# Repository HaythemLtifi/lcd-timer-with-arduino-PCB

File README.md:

# lcd-timer-with-arduino-PCB
Lcd timer with arduino that uses an encoder to set the time.
The code works but its limited , feel free to upgraded
Feel free to review the board.

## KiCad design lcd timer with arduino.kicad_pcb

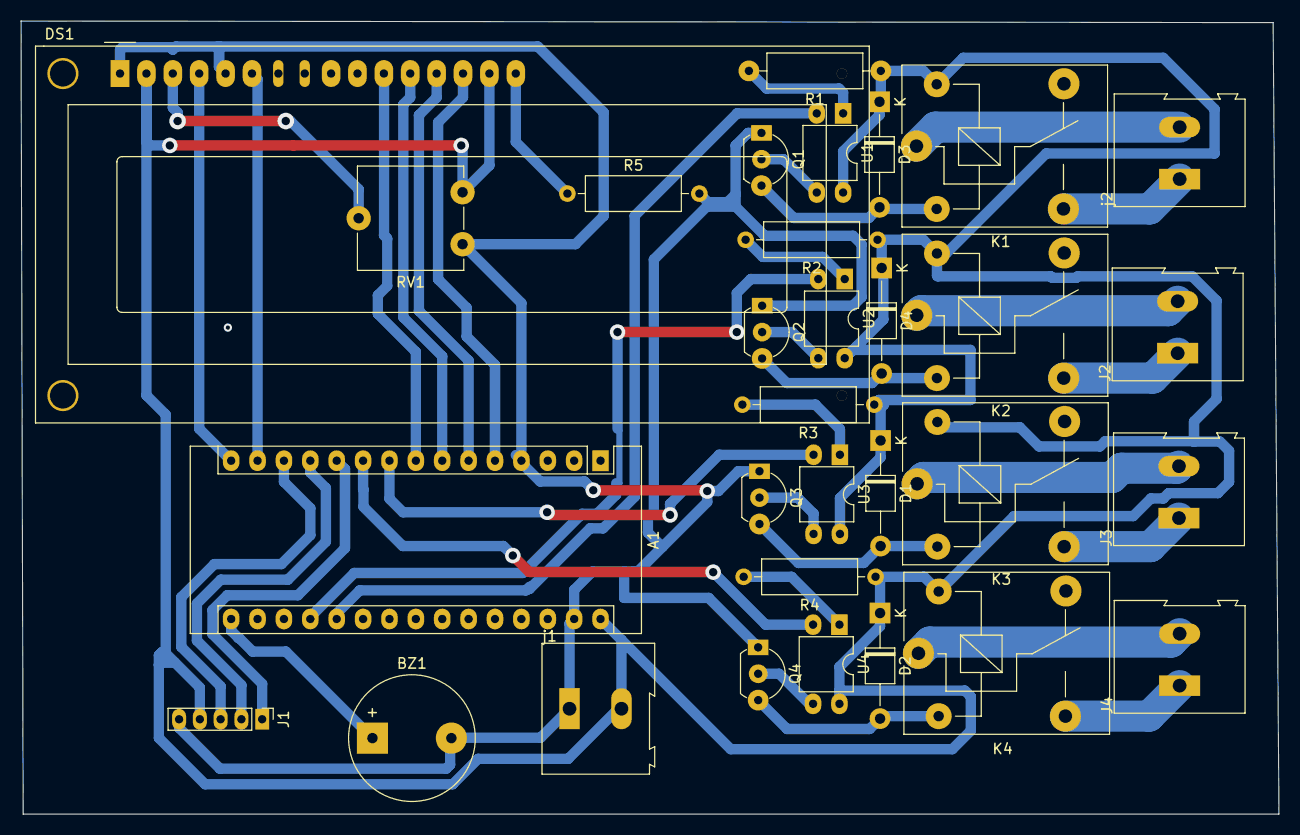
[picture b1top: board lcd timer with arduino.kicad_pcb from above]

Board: 2 copper layers, 121.1 x 76.4 mm, 31 parts (0 on the bottom side), 38 nets.

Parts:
A1: Arduino_Nano_v3.x; Arduino_Nano
BZ1: Buzzer; Buzzer_12x9.5RM7.6
D1, D2, D3, D4: D; D_T-1_P10.16mm_Horizontal
DS1: WC1602A
J1: Conn_01x05_Female; PinHeader_1x05_P2.00mm_Vertical
J2, J3, J4: Screw_Terminal_01x02; TerminalBlock_Altech_AK300-2_P5.00mm
K1, K2, K3, K4: SANYOU_SRD_Form_C; Relay_SPDT_SANYOU_SRD_Series_Form_C
Q1, Q2, Q3, Q4: 2N3904; TO-92L_Inline_Wide
R1, R2, R3, R4: 1k; R_Axial_DIN0309_L9.0mm_D3.2mm_P12.70mm_Horizontal
R5: 220; R_Axial_DIN0309_L9.0mm_D3.2mm_P12.70mm_Horizontal
RV1: R_POT; Potentiometer_ACP_CA9-V10_Vertical
U1, U2, U3, U4: PC817; DIP-4_W7.62mm
j1, j2: Screw_Terminal_01x02; TerminalBlock_Altech_AK300-2_P5.00mm

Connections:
+: A1.30, D1.1, D2.1, D3.1, D4.1, DS1.2, DS1.15, J1.4, K1.5, K2.5, K3.5, K4.5, R1.1, R2.1, R3.1, R4.1, RV1.1, U1.4, U2.4, U3.4, U4.4, j1.2
-: A1.4, A1.29, BZ1.2, DS1.1, DS1.5, J1.5, Q1.1, Q2.1, Q3.1, Q4.1, R5.2, RV1.3, j1.1
D2: A1.5, DS1.14
D3: A1.6, DS1.13
D4: A1.7, DS1.12
D5: A1.8, DS1.11
D11: A1.14, DS1.6
D12: A1.15, DS1.4
unnamed: A1.16, BZ1.1
unnamed: D1.2, K3.2, Q3.3
unnamed: D2.2, K4.2, Q4.3
unnamed: D3.2, K1.2, Q1.3
unnamed: D4.2, K2.2, Q2.3
unnamed: DS1.3, RV1.2
unnamed: DS1.16, R5.1
unnamed: J2.1, K2.3
unnamed: J2.2, K2.1
unnamed: J3.1, K3.3
unnamed: J3.2, K3.1
unnamed: J4.1, K4.3
unnamed: J4.2, K4.1
unnamed: K1.1, j2.2
unnamed: K1.3, j2.1
unnamed: Q1.2, U1.3
unnamed: Q2.2, U2.3
unnamed: Q3.2, U3.3
unnamed: Q4.2, U4.3
unnamed: R1.2, U1.1
unnamed: R2.2, U2.1
unnamed: R3.2, U3.1
unnamed: R4.2, U4.1
clk: A1.11, J1.1
dt: A1.12, J1.2
on1: A1.9, U3.2
on2: A1.10, U4.2
on3: A1.20, U1.2
on4: A1.19, U2.2
sw: A1.13, J1.3

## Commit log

2021-01-28 pcb with no code
2021-01-30 Version2
2021-01-31 thiker traces
2021-02-01 removed acide traps
2021-03-01 fixed the schematic
2021-03-01 code for relais 1 and 4
2021-03-03 MORE COOL IMAGEES
2021-03-03 code for both relais is added
